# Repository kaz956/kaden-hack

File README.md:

# 総合教育セミナー 家電ハック
## About
総合教育セミナー 家電ハックのプロジェクトです．

## 開発環境
- マイコン(Arduino, ESP32)はPlatformIOで開発．
- WebフロントエンドはHTML+JavaScript．
- Google Spreadsheet + Google Apps Script
- PCBはAutodesk Eagleで設計，JLCPCBに発注．
- ハードウェア設計はSolidworks．

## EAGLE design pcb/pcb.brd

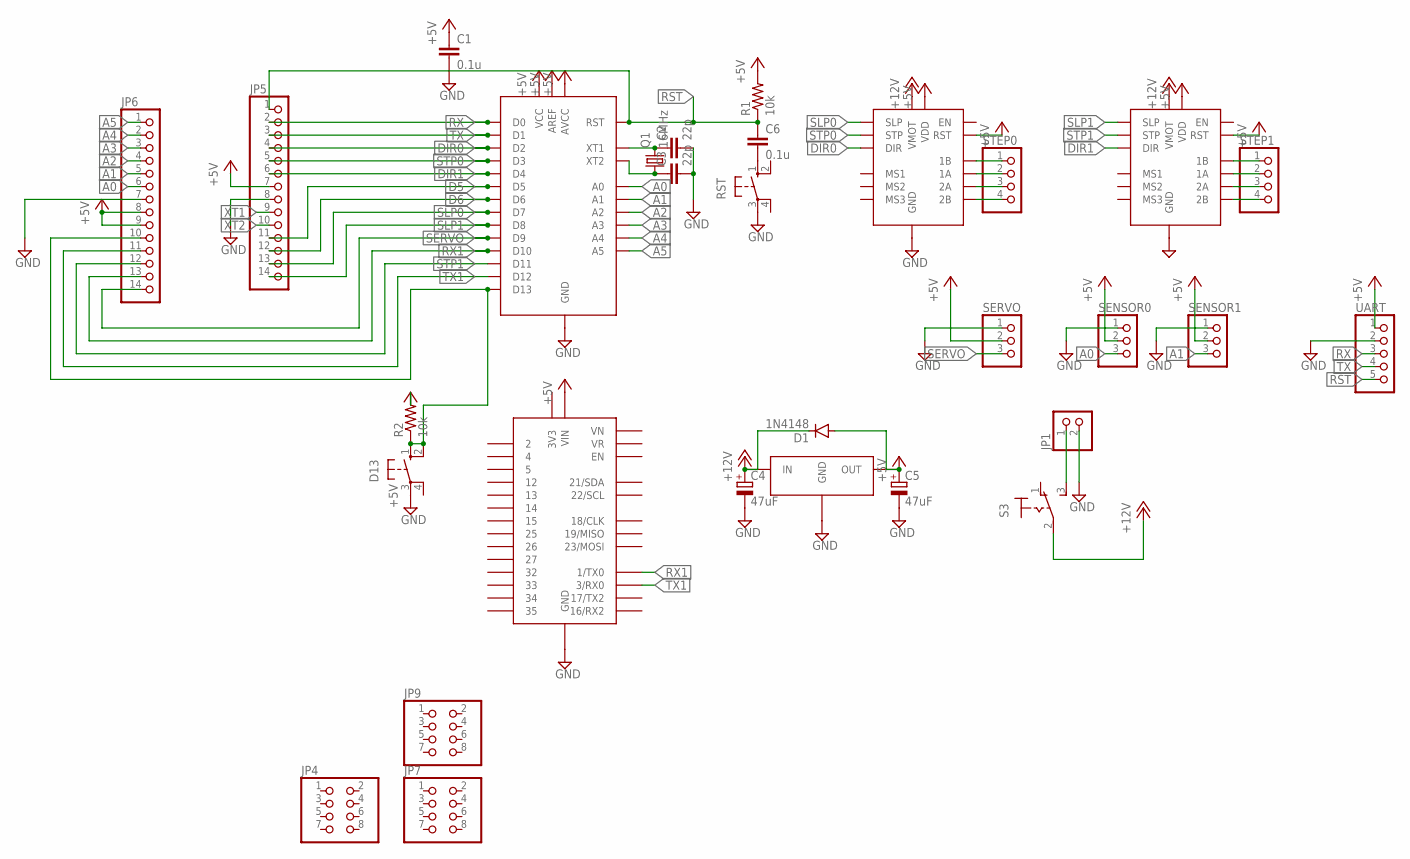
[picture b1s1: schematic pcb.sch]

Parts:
C1, C6: 0.1u; C025-025X050
C2, C3: 22p; C025-025X050
C4, C5: 47uF; E2,5-5
D1: 1N4148; DO35-7
D13: 10-XX; B3F-10XX
IC1: ATMEGA328P-3; DIL28-3
JP1: PINHD-1X2; 1X02
JP4, JP7, JP9: PINHD-2X4; 2X04
JP5, JP6: PINHD-1X14; 1X14
Q1: 16MHz; HC49/S
R1, R2: 10k; 0204/7
RST: 10-XX; B3F-10XX
S3: TOGGLE
SENSOR0, SENSOR1: PINHD-1X3; 1X03
SERVO: PINHD-1X3; 1X03
STEP0, STEP1: PINHD-1X4; 1X04
U$1, U$2: A4988
U$3: NODE32S
U$5: NJM7805
UART: PINHD-1X5; 1X05

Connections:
+5V: C1.1, C5.+, D1.A, IC1.AREF, IC1.AVCC, IC1.VCC, JP5.7, JP6.8, JP6.9, R1.2, R2.2, SENSOR0.2, SENSOR1.2, SERVO.2, U$1.RST, U$1.VDD, U$2.RST, U$2.VDD, U$3.VIN, U$5.OUT, UART.1
+12V: C4.+, D1.C, S3.2, U$1.VMOT, U$2.VMOT, U$5.IN
A0: IC1.A0, JP6.6, SENSOR0.3
A1: IC1.A1, JP6.5, SENSOR1.3
A2: IC1.A2, JP6.4
A3: IC1.A3, JP6.3
A4: IC1.A4, JP6.2
A5: IC1.A5, JP6.1
D5: IC1.D5, JP5.11
D6: IC1.D6, JP5.12
DIR0: IC1.D2, JP5.4, U$1.DIR
DIR1: IC1.D4, JP5.6, U$2.DIR
GND: C1.2, C2.2, C3.2, C4.-, C5.-, D13.3, IC1.GND1 (GND), IC1.GND2 (GND), JP1.2, JP5.8, JP6.7, RST.3, SENSOR0.1, SENSOR1.1, SERVO.1, U$1.GND0 (GND), U$1.GND1 (GND), U$2.GND0 (GND), U$2.GND1 (GND), U$3.GND, U$3.GND1 (GND), U$5.GND, UART.2
unnamed: STEP0.1, U$1.1B
unnamed: STEP0.2, U$1.1A
unnamed: STEP0.3, U$1.2A
unnamed: STEP0.4, U$1.2B
unnamed: C6.2, RST.1 (S)
unnamed: D13.1 (S), D13.2 (S1), IC1.D13, JP6.10, R2.1
unnamed: STEP1.1, U$2.1B
unnamed: STEP1.2, U$2.1A
unnamed: STEP1.3, U$2.2A
unnamed: STEP1.4, U$2.2B
unnamed: JP1.1, S3.3 (S)
RST: C6.1, IC1.RST, JP5.1, R1.1, UART.5
RX: IC1.D0, JP5.2, UART.3
RX1: IC1.D10, JP6.13, U$3.TX0 (1/TX0)
SERVO: IC1.D9, JP6.14, SERVO.3
SLP0: IC1.D7, JP5.13, U$1.SLP
SLP1: IC1.D8, JP5.14, U$2.SLP
STP0: IC1.D3, JP5.5, U$1.STP
STP1: IC1.D11, JP6.12, U$2.STP
TX: IC1.D1, JP5.3, UART.4
TX1: IC1.D12, JP6.11, U$3.RX0 (3/RX0)
XT1: C2.1, IC1.XT1, JP5.9, Q1.2
XT2: C3.1, IC1.XT2, JP5.10, Q1.1

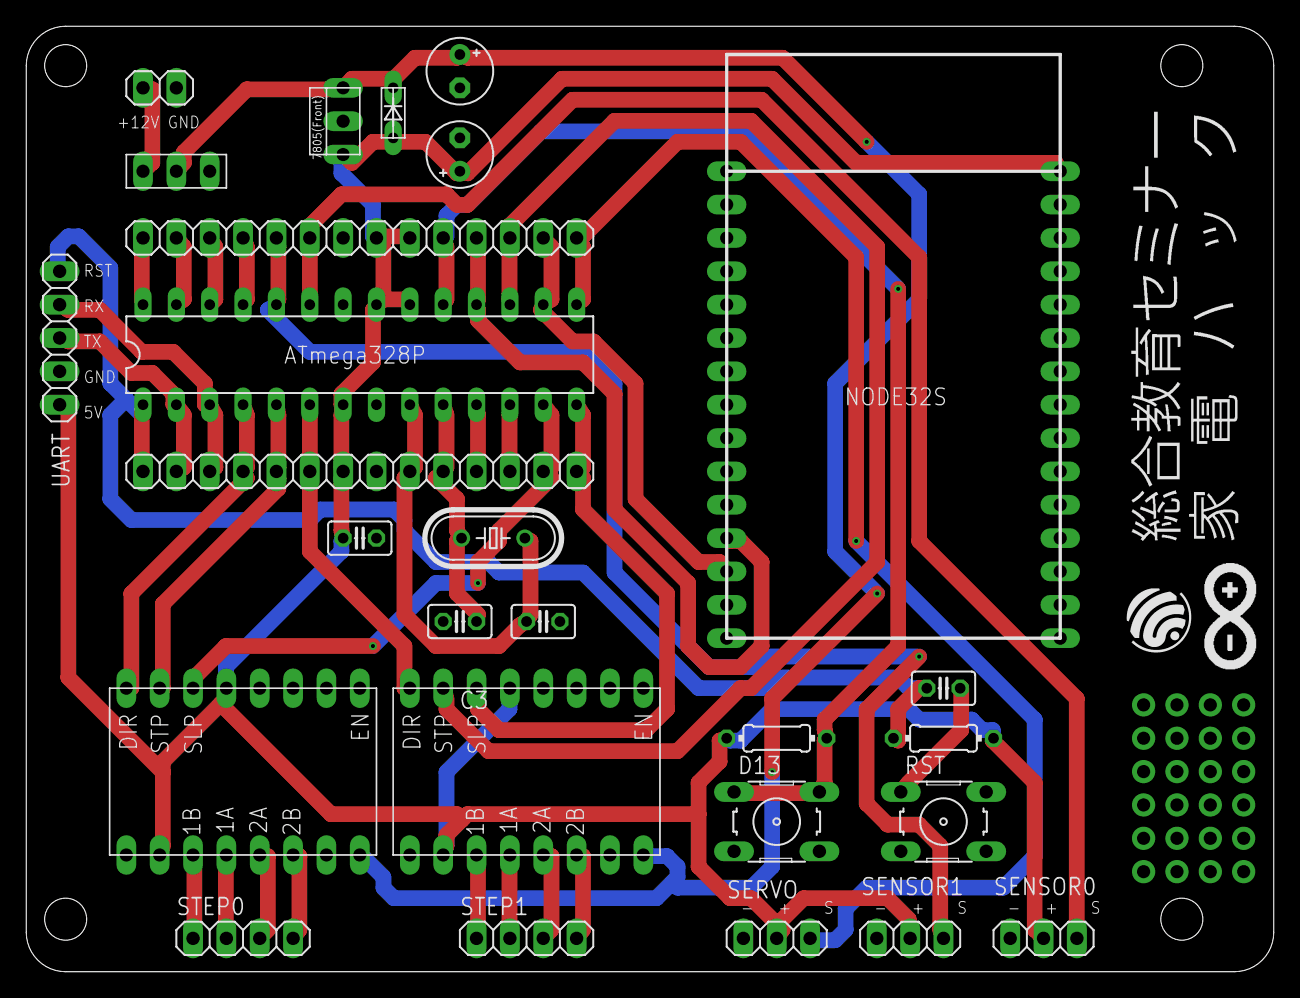
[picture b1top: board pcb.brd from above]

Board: 2 copper layers, 95.0 x 72.0 mm, 30 parts (0 on the bottom side), 36 nets.

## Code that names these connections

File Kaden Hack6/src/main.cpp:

#include <Arduino.h>

const int SERVO = 9;
const int DIR0 = 2;
const int DIR1 = 4;
const int STEP0 = 3;
const int STEP1 = 11;
const int PHR1 = A0;
const int PHR2 = A1;
const int PHR_ANS = 800;
const int RPM_5 = 17;
const int RPM_15 = 51;
const int RPM_30 = 103;
const int RPM_45 = 154;
const int RPM_60 = 205;
const int RPM_75 = 257;
const int RPM_90 = 308;
const int RPM_105 = 359;
const int RPM_120 = 411;
const int RPM_135 = 462;
const int RPM_150 = 513;
const int BACK = 200;
const int JET = 333;
const int SLP0 = 7;
const int SLP1 = 8;
const int RX = 10;
const int TX = 12;

int ans1;
int ans2;
int ans3;
int p = 1;
int runcnt=0;

void setup()
{
  // cli();
  // TCCR1A  = 0;
  // TCCR1B  = 0;  //12ビット
  // TCNT1 = 0;  //???
  // TCCR1B |= (1 << WGM12) | (1 << CS10) | (1 << CS12);  //CTC 分周1024  
  // OCR1A   = 46875-1;
  // TIMSK1 |= (1 << OCIE1A);
  // sei();

  Serial.begin(9600); // 9600bpsでシリアル通信のポートを開きます
  pinMode(PHR1, INPUT);
  pinMode(PHR2, INPUT);
  pinMode(RX, INPUT);
  pinMode(SERVO,OUTPUT);
  pinMode(DIR0, OUTPUT);
  pinMode(DIR1, OUTPUT);
  pinMode(STEP0, OUTPUT);
  pinMode(STEP1, OUTPUT);
  pinMode(SLP0,OUTPUT);
  pinMode(SLP1,OUTPUT);
  pinMode(TX,OUTPUT);
  digitalWrite(SLP0, LOW);
  digitalWrite(SLP1, LOW);
}

void read_sensor(){
  ans1 = analogRead(PHR1);
  ans2 = analogRead(PHR2);
  Serial.println(ans1);
  Serial.println(ans2); // シリアルモニターに表示させる
}

void cw()
{
  for(int k = 500; k <= 2400; k += 10){
    digitalWrite(SERVO,HIGH);
    delayMicroseconds(k);
    digitalWrite(SERVO,LOW);
    delayMicroseconds(20000-k);
  }
}

void ccw()
{
  for(int k = 2400; k >= 500; k -= 10){
    digitalWrite(SERVO,HIGH);
    delayMicroseconds(k);
    digitalWrite(SERVO,LOW);
    delayMicroseconds(20000-k);
  }
}

void jet_stop()
{
  digitalWrite(SERVO,HIGH);
  delayMicroseconds(500);
  digitalWrite(SERVO,LOW);
  delayMicroseconds(19500);
}

void jet()
{
  if(runcnt>=10){
    cw();
    delay(300);
    ccw();
    delay(600);
    runcnt=0;
  }
}

void stop()
{
  digitalWrite(DIR0, HIGH);
  digitalWrite(DIR1, HIGH);
  digitalWrite(STEP0, HIGH);
  digitalWrite(STEP1, HIGH);
}

void go_forward()
{
    digitalWrite(DIR0, LOW);
    digitalWrite(DIR1, HIGH);
    digitalWrite(STEP0, HIGH);
    digitalWrite(STEP1, HIGH);
    delay(5);
    digitalWrite(STEP0, LOW);
    digitalWrite(STEP1, LOW);
    delay(4);
}

void go_back()
{
  digitalWrite(DIR0, HIGH);
  digitalWrite(DIR1, LOW);
  for (int i = 0; i < BACK; i++)
  {
    digitalWrite(STEP0, HIGH);
    digitalWrite(STEP1, HIGH);
    delay(5);
    digitalWrite(STEP0, LOW);
    digitalWrite(STEP1, LOW);
    delay(4);
  }
}

void turn_right_5()
{
  digitalWrite(DIR0, HIGH);
  digitalWrite(DIR1, HIGH);
  digitalWrite(STEP1, HIGH);

  for (int i = 0; i < RPM_5; i++)
  {
    digitalWrite(STEP0, HIGH);
    delay(6);
    digitalWrite(STEP0, LOW);
    delay(6);
  }
}

void turn_right_90()
{
  digitalWrite(DIR0, HIGH);
  digitalWrite(DIR1, HIGH);
  digitalWrite(STEP0, HIGH);

  for (int i = 0; i < RPM_90; i++)
  {
    digitalWrite(STEP1, HIGH);
    delay(6);
    digitalWrite(STEP1, LOW);
    delay(6);
  }
}

void turn_left_5()
{
  digitalWrite(DIR0, LOW);
  digitalWrite(DIR1, LOW);
  digitalWrite(STEP0, HIGH);

  for (int i = 0; i < RPM_5; i++)
  {
    digitalWrite(STEP1, HIGH);
    delay(6);
    digitalWrite(STEP1, LOW);
    delay(6);
  }
}

void turn_left_90()
{
  digitalWrite(DIR0, LOW);
  digitalWrite(DIR1, LOW);
  digitalWrite(STEP1, HIGH);

  for (int i = 0; i < RPM_90; i++)
  {
    digitalWrite(STEP0, HIGH);
    delay(6);
    digitalWrite(STEP0, LOW);
    delay(6);
  }
}

void drive()
{
  if (ans1 < PHR_ANS && ans2 < PHR_ANS)
  {
    go_forward();
    // read_sensor();
  }
  else if (ans1 < PHR_ANS && ans2 >= PHR_ANS)
  {
    turn_left_5();
    // read_sensor();
  }
  else if (ans1 >= PHR_ANS && ans2 < PHR_ANS)
  {
    turn_right_5();
    // read_sensor();
  }
}

void rotate_right()
{
      turn_right_90();
      read_sensor();
      if (ans1 < PHR_ANS && ans2 < PHR_ANS)
      {
        turn_right_90();
      }

      else if (ans1 >= PHR_ANS && ans2 >= PHR_ANS)
      {
        turn_right_90();
        drive();
        if (ans1 >= PHR_ANS && ans2 >= PHR_ANS)
        {
          stop();
          jet_stop();
          digitalWrite(TX,HIGH);
        }
      } 
}

void rotate_left()
{
  turn_left_90();
  read_sensor();
      if (ans1 < PHR_ANS && ans2 < PHR_ANS)
      {
        turn_left_90();
      }

      else if (ans1 >= PHR_ANS && ans2 >= PHR_ANS)
      {
        turn_left_90();
        drive();
        if (ans1 >= PHR_ANS && ans2 >= PHR_ANS)
        {
          stop();
          jet_stop();
          digitalWrite(TX,HIGH);
        }
      } 
}

void run()
{
  if (ans1 >= PHR_ANS && ans2 >= PHR_ANS)
  {
    go_back();

    if(p==1)
    {
      rotate_right();   
      p=2;
    }
    
    else if(p==2)
    {
      rotate_left();
      p=1;
    }
  }
  else if (ans1 < PHR_ANS && ans2 < PHR_ANS)
  {
    go_forward();
    // read_sensor();
  }
  else if (ans1 < PHR_ANS && ans2 >= PHR_ANS)
  {
    turn_left_5();
    // read_sensor();
  }
  else if (ans1 >= PHR_ANS && ans2 < PHR_ANS)
  {
    turn_right_5();
    // read_sensor();
  }
  for(int l=0;l<27;l++){
    go_forward();
  }
  runcnt++;
}


/*
ISR (TIMER1_COMPA_vect) {
  jet();
}
*/

void loop()
{
  /*
  while(1);
  // put your main code here, to run repeatedly:
  delay(50);           // 250ms時間待ちで繰り返す
  */

  while(1){
    ans3 = digitalRead(RX);
    if(ans3 == 1){
      digitalWrite(SLP0, HIGH);
      digitalWrite(SLP1, HIGH); 
      break;
    }
  }  

  while(1){
      if(digitalRead(RX)==0){
        break;
      }
      run();
      read_sensor();
      jet();
  }
  
  digitalWrite(SLP0, LOW);
  digitalWrite(SLP1, LOW); 
  digitalWrite(TX,HIGH);
  /*
  if (ans1 >= PHR_ANS && ans2 >= PHR_ANS)
  {
    stop();
  }
  */

}

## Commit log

2022-01-13 add eagle project
2022-01-13 add esp32 platformio project
2022-01-13 add web html
2022-01-13 changed directory name properly
2022-01-13 add readme
2022-01-13 Create hardware
2022-01-13 Create deleteMeAfterUpload
2022-01-18 角度実験用
2022-01-19 るんばのはーどうぇあ
